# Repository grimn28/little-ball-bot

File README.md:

# little-ball-bot

This is a project to build a small ball-balancing robot.  The intent is to make a smaller version of the "Rezero" robot - something that will move around on a desk.  So far, I have made a high-level dynamics and controls model in MATLAB, and I've made a driver for the IMU that I plan to use.  More MATLAB modeling to come, followed by C/C++ implementation on an MBED LPC1768.

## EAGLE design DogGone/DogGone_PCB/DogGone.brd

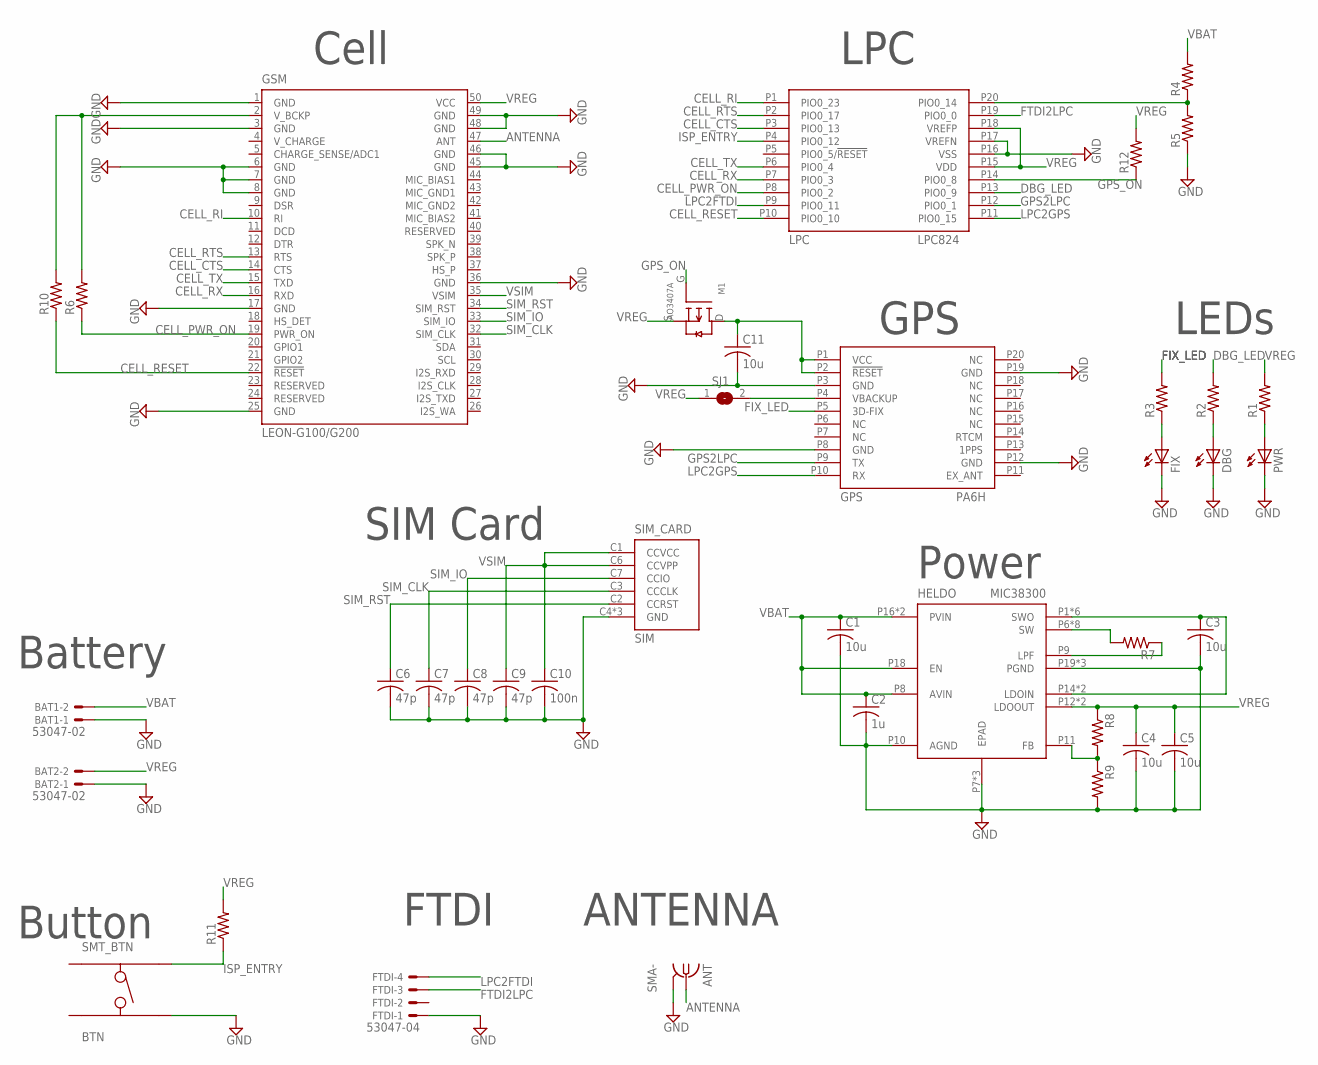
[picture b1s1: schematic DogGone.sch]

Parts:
ANT: SMA-; J502-ND-142-0701-801/806
BAT1, BAT2: 53047-02
BTN: SMT_BTN; SMT_BUTTON
C1, C3, C4, C5, C11: 10u; 0603
C2: 1u; 0603
C6, C7, C8, C9: 47p; 0603
C10: 100n; 0603
DBG: LEDCHIPLED_0603; CHIPLED_0603
FIX: LEDCHIPLED_0603; CHIPLED_0603
FTDI: 53047-04
GPS: PA6H; DFN20
GSM: LEON-G100/G200
HELDO: MIC38300; MLF
LPC: LPC824; TSSOP20
M1: AO3407A; SOT23
PWR: LEDCHIPLED_0603; CHIPLED_0603
R1, R2, R3, R4, R5, R6, R7, R8, R9, R10, R11, R12: R0603
SIM: SIM_CARD; SIM8050
SJ1: SJ

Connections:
ADC_IN: LPC.P20 (PIO0_14), R4.1, R5.2
ANTENNA: ANT.1, GSM.47 (ANT)
CELL_CTS: GSM.14 (CTS), LPC.P3 (PIO0_13)
CELL_PWR_ON: GSM.19 (PWR_ON), LPC.P8 (PIO0_2), R6.1
CELL_RESET: GSM.22 (!RESET), LPC.P10 (PIO0_10), R10.1
CELL_RI: GSM.10 (RI), LPC.P1 (PIO0_23)
CELL_RTS: GSM.13 (RTS), LPC.P2 (PIO0_17)
CELL_RX: GSM.16 (RXD), LPC.P7 (PIO0_3)
CELL_TX: GSM.15 (TXD), LPC.P6 (PIO0_4)
DBG_LED: LPC.P13 (PIO0_9), R2.2
FB: HELDO.P11 (FB), R8.2, R9.1
FIX_LED: GPS.P5 (3D-FIX), R3.2
FTDI2LPC: FTDI.3, LPC.P19 (PIO0_0)
GND: ANT.G@1 (GND), ANT.G@2 (GND), ANT.G@3 (GND), ANT.G@4 (GND), BAT1.1, BAT2.1, BTN.P4, C1.2, C2.2, C3.2, C4.2, C5.2, C6.2, C7.2, C8.2, C9.2, C10.2, C11.2, DBG.C, FIX.C, FTDI.1, GPS.P3 (GND), GPS.P8 (GND), GPS.P12 (GND), GPS.P19 (GND), GSM.1 (GND), GSM.3 (GND), GSM.6 (GND), GSM.7 (GND), GSM.8 (GND), GSM.17 (GND), GSM.25 (GND), GSM.36 (GND), GSM.45 (GND), GSM.46 (GND), GSM.48 (GND), GSM.49 (GND), HELDO.P7 (EPAD), HELDO.P8-21 (EPAD), HELDO.P10 (AGND), HELDO.P19 (PGND), HELDO.P20 (PGND), HELDO.P21 (PGND), HELDO.P22 (EPAD), LPC.P16 (VSS), LPC.P17 (VREFN), PWR.C, R5.1, R9.2, SIM.C4 (GND), SIM.C5 (GND), SIM.C8 (GND)
GPS2LPC: GPS.P9 (TX), LPC.P12 (PIO0_1)
GPS_ON: LPC.P14 (PIO0_8), M1.G, R12.1
ISP_ENTRY: BTN.P2, LPC.P4 (PIO0_12), R11.1
LPC2FTDI: FTDI.4, LPC.P9 (PIO0_11)
LPC2GPS: GPS.P10 (RX), LPC.P11 (PIO0_15)
LPF: HELDO.P9 (LPF), R7.1
unnamed: PWR.A, R1.1
unnamed: GPS.P4 (VBACKUP), SJ1.2
unnamed: C11.1, GPS.P1 (VCC), GPS.P2 (!RESET), M1.D
unnamed: FIX.A, R3.1
unnamed: DBG.A, R2.1
SIM_CLK: C7.1, GSM.32 (SIM_CLK), SIM.C3 (CCCLK)
SIM_IO: C8.1, GSM.33 (SIM_IO), SIM.C7 (CCIO)
SIM_RST: C6.1, GSM.34 (SIM_RST), SIM.C2 (CCRST)
SW: HELDO.P6 (SW), HELDO.P23 (SW), HELDO.P23-28 (SW), HELDO.P24 (SW), HELDO.P25 (SW), HELDO.P26 (SW), HELDO.P27 (SW), HELDO.P28 (SW), R7.2
SWO: C3.1, HELDO.P1 (SWO), HELDO.P1-5 (SWO), HELDO.P2 (SWO), HELDO.P3 (SWO), HELDO.P4 (SWO), HELDO.P5 (SWO), HELDO.P14 (LDOIN), HELDO.P15 (LDOIN)
VBAT: BAT1.2, C1.1, C2.1, HELDO.P8 (AVIN), HELDO.P16 (PVIN), HELDO.P17 (PVIN), HELDO.P18 (EN), R4.2
VREG: BAT2.2, C4.1, C5.1, GSM.50 (VCC), HELDO.P12 (LDOOUT), HELDO.P13 (LDOOUT), LPC.P15 (VDD), LPC.P18 (VREFP), M1.S, R1.2, R8.1, R11.2, R12.2, SJ1.1
VSIM: C9.1, C10.1, GSM.35 (VSIM), SIM.C1 (CCVCC), SIM.C6 (CCVPP)
V_BCKP: GSM.2 (V_BCKP), R6.2, R10.2

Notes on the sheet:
Cell
LPC
GPS
Power
SIM Card
Battery
LEDs
Button
ANTENNA
FTDI

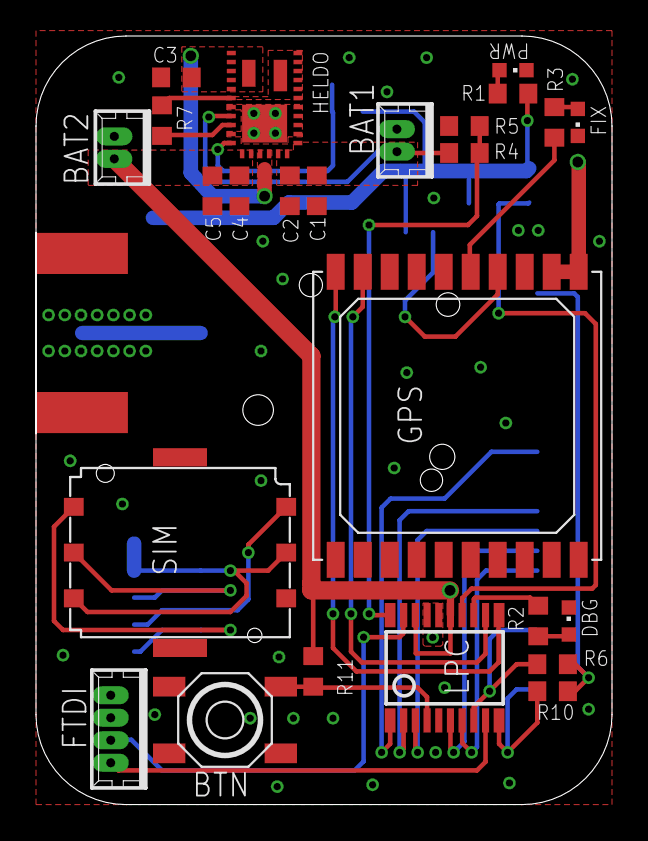
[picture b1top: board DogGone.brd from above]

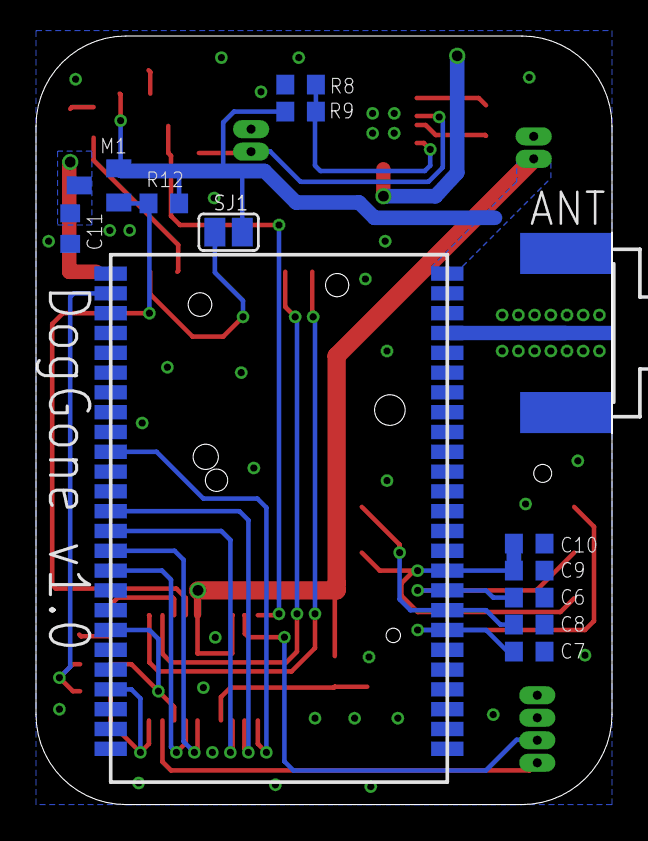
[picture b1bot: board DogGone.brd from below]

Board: 2 copper layers, 32.0 x 42.7 mm, 39 parts (13 on the bottom side), 34 nets.

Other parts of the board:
DRILEGEND: DRILEGEND

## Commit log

2015-05-17 some more description in the README
2015-05-17 first commit of all projects
2015-05-17 third first commit *sigh*
2015-05-17 cleared out non-project stuff
2015-05-17 organizing by file type
2015-05-17 added subdirectories
2015-05-17 added readme
2015-05-17 added documentation
2015-05-17 insignificant change in doc
2015-05-17 comment in sensor function
2015-05-17 fiddling...
2015-05-18 setting up for kalman estimator
2015-05-19 changed some names. commented out kalman junk
2015-05-19 changed names
2015-05-27 fixed typo in doc, gutted continuous model, created discrete model
2015-05-27 added the discrete model...again
2015-05-27 made the PID more "filtery"
2015-05-27 Added noise. Preparing for Kalman.
2015-05-27 kalman estimated state feedback + PID control. This is a good working model.
2015-05-27 started the animation.
2015-05-27 added animation
2015-05-29 added motor speed command inputs. changed doc format
2015-05-29 changed doc format
